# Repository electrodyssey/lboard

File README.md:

# lboard
Very basic Spartan-6 LX9 board with a plenty of GPIO
This was my very first attempt to dive into fpga world.
Board is working, however it has a few disadvantages:
Configuration is loaded via slave select-map setup which occupies a lot of fpga pins
Configuration is slow - around 3 seconds. That's an outcome of Atmega's slow gpio
There is no switched step-down psu on the board, power is regulated with a linear ldo

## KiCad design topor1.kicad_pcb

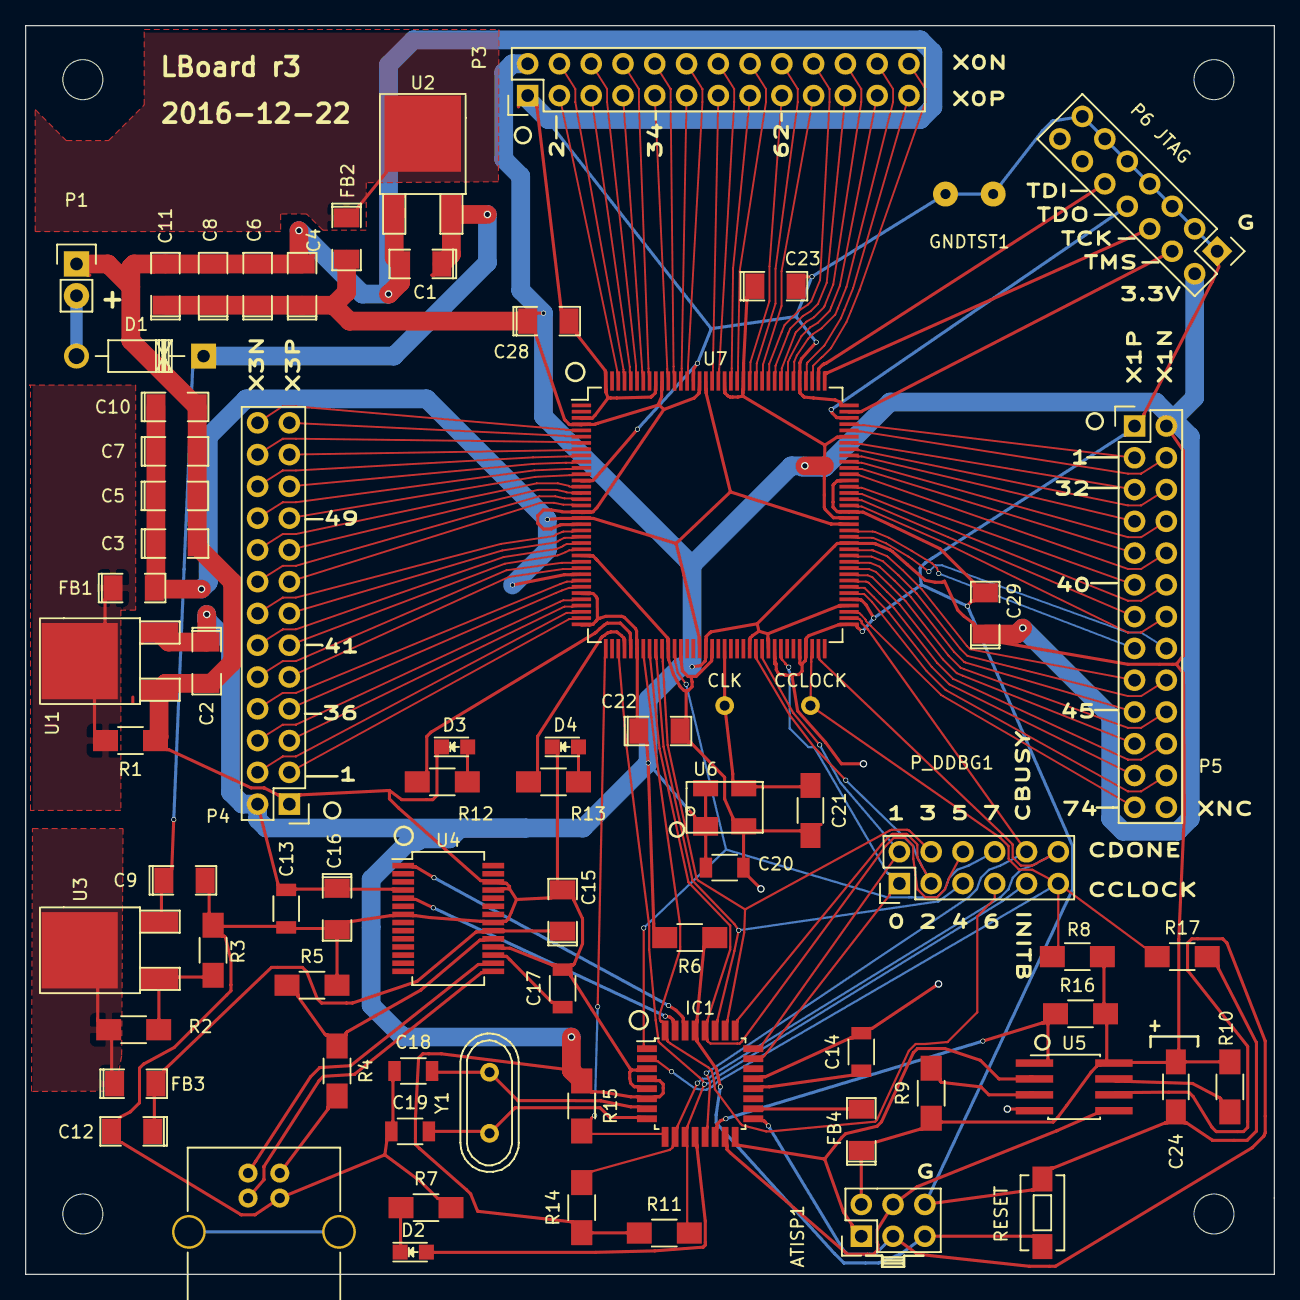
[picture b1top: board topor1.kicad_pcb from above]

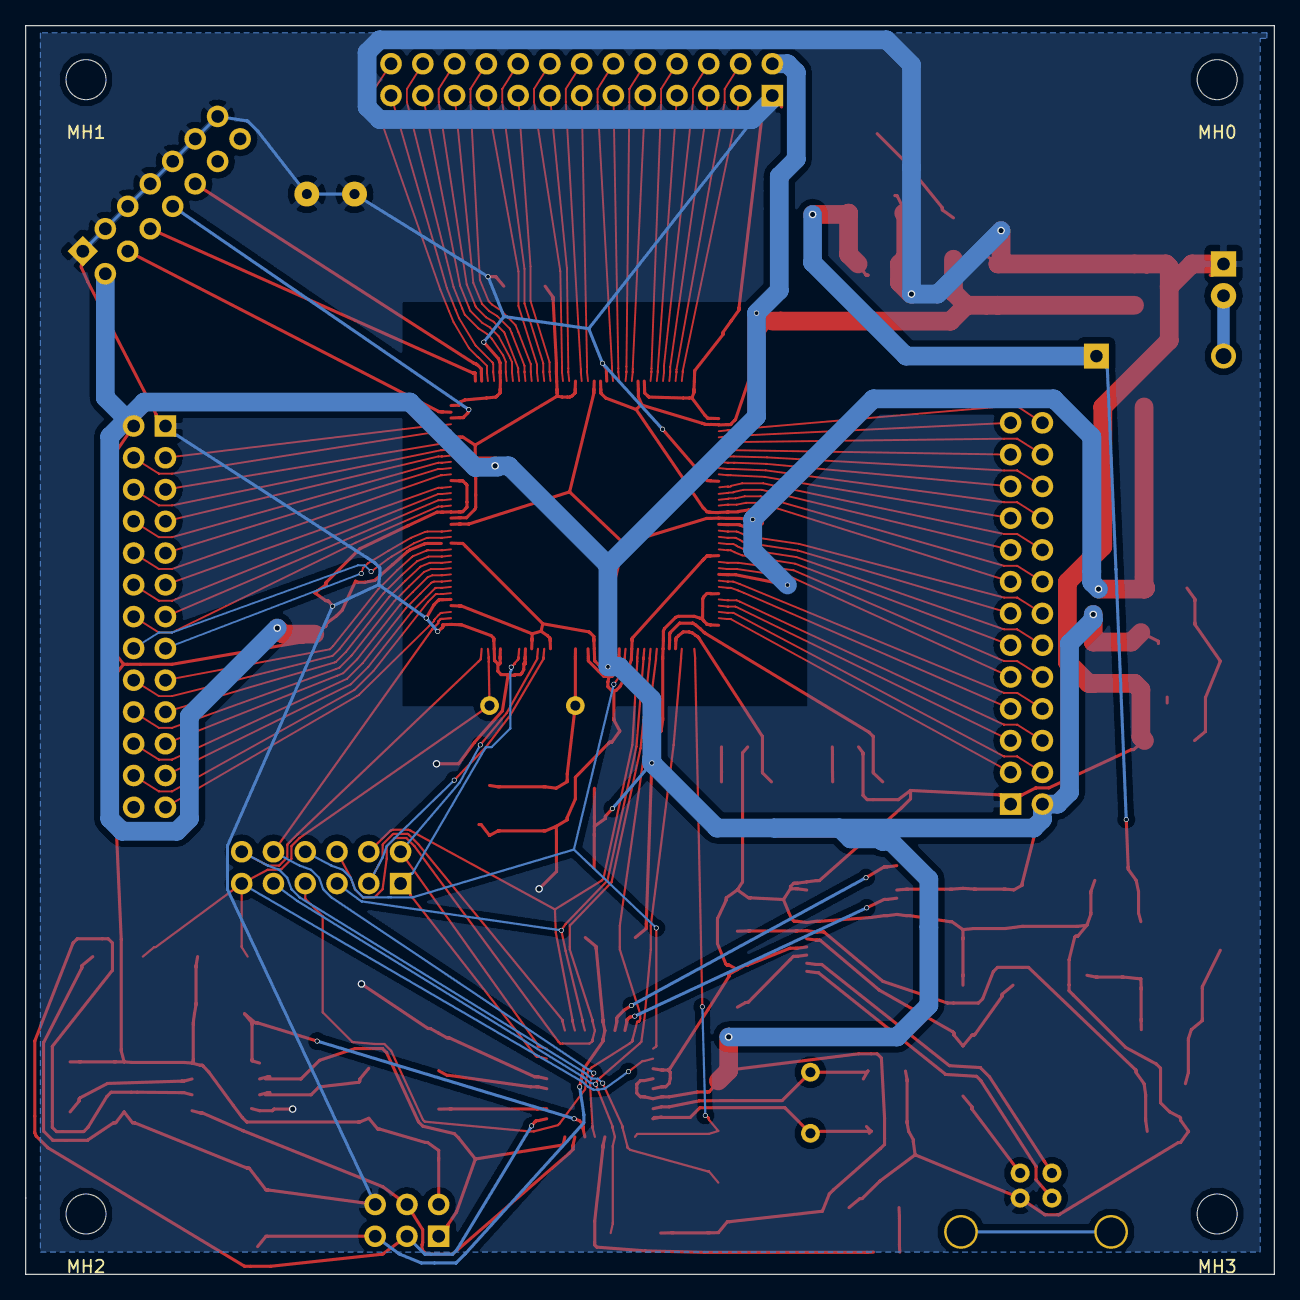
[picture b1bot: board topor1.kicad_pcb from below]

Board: 2 copper layers, 99.8 x 99.8 mm, 76 parts (4 on the bottom side), 123 nets.

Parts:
ATISP1: AVR-ISP-6; Pin_Header_Straight_2x03
C1, C2, C5, C6, C7, C8, C9, C10, C11, C22, C23, C28, C29: 10uF; SMD-1206_Pol
C3, C4, C12, C15, C16: 1uF; SMD-1206_Pol
C13, C14, C17, C20: 0.1; C_1206
C18, C19: 15pF; C_1206
C21: 15pF; C_1206_HandSoldering
C24: 1uF; C_1206_HandSoldering
CCLOCK: TEST_1P; Measurement_Point_Round-TH_Small
CLK: TEST_1P; Measurement_Point_Round-TH_Small
D1: D_Rectifier; Diode_DO-41_SOD81_Horizontal_RM10
D2: LED; LED_0805
D3, D4: Led_Small; LED_0805
FB1, FB2, FB3, FB4: FERRITE; SMD-1206_Pol
GNDTST1: TEST; SolderWirePad_2x_0-8mmDrill
IC1: ATMEGA168-A; TQFP-32_7x7mm_Pitch0.8mm
MH0, MH1, MH2, MH3: MountingHole_3.2mm_M3
P1: CONN_01X02_PWR; Pin_Header_Straight_1x02
P2: USB_B
P3: CONN_02X13_X0; Pin_Header_Straight_2x13
P4: CONN_02X13_X3; Pin_Header_Straight_2x13
P5: CONN_02X13_X1; Pin_Header_Straight_2x13
P6 JTAG: CONN_02X07_JTAG; Pin_Header_Straight_2x07
P_DDBG1: CONN_02X06; Pin_Header_Straight_2x06
R1, R2: 121; R_1206_HandSoldering
R3: 365; R_1206_HandSoldering
R4, R11, R15: 4k7; R_1206_HandSoldering
R5, R6, R8, R9, R10: 10k; R_1206_HandSoldering
R7: 220; R_1206_HandSoldering
R12, R13, R14: 330; R_1206_HandSoldering
R16, R17: 100; R_1206_HandSoldering
RESET: SW_RESET; SW_SPST_EVQPE1
U1, U3: AP1117_ADJ; TO-252-2Lead
U2: AP1117_33; TO-252-2Lead
U4: FT232RL; SSOP-28_5.3x10.2mm_Pitch0.65mm
U5: M25P16-VME; SOIC-8_5.49x5.49mm_Pitch1.27mm
U6: ECS-3963; ECS396x
U7: XC6SLX9-TQG144; LQFP-144_20x20mm_Pitch0.5mm
Y1: 11.059MHz; Crystal_HC49-U_Vertical

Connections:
+1V2: C3.1, C5.1, C7.1, C10.1, FB1.2, U7.19, U7.28, U7.52, U7.89, U7.128
+3V3: ATISP1.2, C2.1, C4.1, C6.1, C8.1, C11.1, C13.1, C16.1, C20.1, C22.1, C23.1, C24.2, C28.1, C29.1, FB2.2, FB4.1, IC1.4, IC1.6, P3.2, P4.2, P5.2, P6 JTAG.2, R6.2, R8.2, R9.1, R10.1, R11.1, R14.1, R15.1, R16.1, U1.3, U4.4, U5.8, U6.1, U6.4, U7.4, U7.18, U7.20, U7.31, U7.36, U7.42, U7.53, U7.60, U7.63, U7.76, U7.86, U7.90, U7.103, U7.122, U7.125, U7.129, U7.135
+5V: C12.1, C15.1, FB3.2, U4.20
/mcu/CBUSY: IC1.13, P_DDBG1.10, U7.74
/mcu/CCLOCK: CCLOCK.1, IC1.2, P_DDBG1.11, R16.2, R17.1, U7.70
/mcu/CD0: IC1.23, P_DDBG1.1, U7.65
/mcu/CD1: IC1.24, P_DDBG1.2, U7.62
/mcu/CD2: IC1.25, P_DDBG1.3, U7.61
/mcu/CD3: IC1.26, P_DDBG1.4, U7.46
/mcu/CD4: IC1.27, P_DDBG1.5, U7.45
/mcu/CD5: IC1.28, P_DDBG1.6, U7.44
/mcu/CD6: IC1.32, P_DDBG1.7, U7.43
/mcu/CD7: IC1.1, P_DDBG1.8, U7.48
/mcu/CDONE: IC1.10, P_DDBG1.12, R14.2, U7.71
/mcu/CINITB: IC1.11, P_DDBG1.9, R11.2, U7.39
/mcu/CPROGB: IC1.9, R15.2, U7.37
/mcu/MISO: ATISP1.1, IC1.16, U5.2
/mcu/MOSI: ATISP1.4, IC1.15, U5.5
/spartan6/CLK_XO: C21.1, CLK.1, U6.3, U7.56
/spartan6/TCK: P6 JTAG.6, U7.109
/spartan6/TDI: P6 JTAG.10, U7.110
/spartan6/TDO: P6 JTAG.8, U7.106
/spartan6/TMS: P6 JTAG.4, U7.107
/spartan6/X0_L2_N: P3.4, U7.141
/spartan6/X0_L2_P: P3.3, U7.142
/spartan6/X0_L3_N: P3.6, U7.139
/spartan6/X0_L3_P: P3.5, U7.140
/spartan6/X0_L4_N: P3.8, U7.137
/spartan6/X0_L4_P: P3.7, U7.138
/spartan6/X0_L34_N: P3.10, U7.133
/spartan6/X0_L34_P: P3.9, U7.134
/spartan6/X0_L35_N: P3.12, U7.131
/spartan6/X0_L35_P: P3.11, U7.132
/spartan6/X0_L36_N: P3.14, U7.126
/spartan6/X0_L36_P: P3.13, U7.127
/spartan6/X0_L37_N: P3.16, U7.123
/spartan6/X0_L37_P: P3.15, U7.124
/spartan6/X0_L62_N: P3.18, U7.120
/spartan6/X0_L62_P: P3.17, U7.121
/spartan6/X0_L63_N: P3.20, U7.118
/spartan6/X0_L63_P: P3.19, U7.119
/spartan6/X0_L64_N: P3.22, U7.116
/spartan6/X0_L64_P: P3.21, U7.117
/spartan6/X0_L65_N: P3.24, U7.114
/spartan6/X0_L65_P: P3.23, U7.115
/spartan6/X0_L66_N: P3.26, U7.111
/spartan6/X0_L66_P: P3.25, U7.112
/spartan6/X1_L1_N: P5.4, U7.104
/spartan6/X1_L1_P: P5.3, U7.105
/spartan6/X1_L32_N: P5.6, U7.101
/spartan6/X1_L32_P: P5.5, U7.102
/spartan6/X1_L33_N: P5.8, U7.99
/spartan6/X1_L33_P: P5.7, U7.100
/spartan6/X1_L34_N: P5.10, U7.97
/spartan6/X1_L34_P: P5.9, U7.98
/spartan6/X1_L40_N: P5.12, U7.94
/spartan6/X1_L40_P: P5.11, U7.95
/spartan6/X1_L41_N: P5.14, U7.92
/spartan6/X1_L41_P: P5.13, U7.93
/spartan6/X1_L42_N: P5.16, U7.87
/spartan6/X1_L42_P: P5.15, U7.88
/spartan6/X1_L43_N: P5.18, U7.84
/spartan6/X1_L43_P: P5.17, U7.85
/spartan6/X1_L45_N: P5.20, U7.82
/spartan6/X1_L45_P: P5.19, U7.83
/spartan6/X1_L46_N: P5.22, U7.80
/spartan6/X1_L46_P: P5.21, U7.81
/spartan6/X1_L47_N: P5.24, U7.78
/spartan6/X1_L47_P: P5.23, U7.79
/spartan6/X1_L74_P: P5.25, U7.75
/spartan6/X3_L1_N: P4.4, U7.34
/spartan6/X3_L1_P: P4.3, U7.35
/spartan6/X3_L2_N: P4.6, U7.32
/spartan6/X3_L2_P: P4.5, U7.33
/spartan6/X3_L36_N: P4.8, U7.29
/spartan6/X3_L36_P: P4.7, U7.30
/spartan6/X3_L37_N: P4.10, U7.26
/spartan6/X3_L37_P: P4.9, U7.27
/spartan6/X3_L41_N: P4.12, U7.23
/spartan6/X3_L41_P: P4.11, U7.24
/spartan6/X3_L42_N: P4.14, U7.21
/spartan6/X3_L42_P: P4.13, U7.22
/spartan6/X3_L43_N: P4.16, U7.16
/spartan6/X3_L43_P: P4.15, U7.17
/spartan6/X3_L44_N: P4.18, U7.14
/spartan6/X3_L44_P: P4.17, U7.15
/spartan6/X3_L49_N: P4.20, U7.11
/spartan6/X3_L49_P: P4.19, U7.12
/spartan6/X3_L50_N: P4.22, U7.9
/spartan6/X3_L50_P: P4.21, U7.10
/spartan6/X3_L51_N: P4.24, U7.7
/spartan6/X3_L51_P: P4.23, U7.8
/spartan6/X3_L52_N: P4.26, U7.5
/spartan6/X3_L52_P: P4.25, U7.6
GND: ATISP1.6, C1.2, C2.2, C3.2, C4.2, C5.2, C6.2, C7.2, C8.2, C9.2, C10.2, C11.2, C12.2, C13.2, C14.2, C15.2, C16.2, C17.2, C18.1, C19.1, C20.2, C21.2, C22.2, C23.2, C24.1, C28.2, C29.2, D3.1, D4.1, GNDTST1.1, IC1.3, IC1.5, IC1.21, P1.1, P2.4, P3.1, P4.1, P5.1, P6 JTAG.1, P6 JTAG.3, P6 JTAG.5, P6 JTAG.7, P6 JTAG.9, P6 JTAG.11, P6 JTAG.13, R1.1, R3.2, R5.2, R7.2, R17.2, RESET.2, U1.1, U2.1, U4.7, U4.18, U4.21, U4.25, U4.26, U5.4, U6.2, U7.3, U7.13, U7.25, U7.47, U7.49, U7.54, U7.64, U7.68, U7.69, U7.73, U7.77, U7.91, U7.96, U7.108, U7.113, U7.130, U7.136, U7.144
unnamed: ATISP1.3, IC1.17, U5.6
unnamed: ATISP1.5, IC1.29, R6.1, RESET.1
unnamed: C14.1, IC1.20
unnamed: C17.1, U4.17
unnamed: C18.2, IC1.7, Y1.2
unnamed: C19.2, IC1.8, Y1.1
unnamed: D1.2, P1.2
unnamed: D2.1, R7.1
unnamed: D2.2, IC1.12
unnamed: D3.2, R12.2
unnamed: D4.2, R13.2
unnamed: FB1.1, R1.2, U1.2
unnamed: FB2.1, U2.2
unnamed: FB3.1, R2.1, U3.2
unnamed: FB4.2, IC1.18
unnamed: IC1.14, R8.1, U5.1
unnamed: IC1.30, U4.1
unnamed: IC1.31, U4.5
unnamed: P2.1, R4.2
unnamed: P2.2, U4.16
unnamed: P2.3, U4.15
unnamed: R2.2, R3.1, U3.1
unnamed: R4.1, R5.1, U4.19
unnamed: R9.2, U5.3
unnamed: R10.2, U5.7
unnamed: R12.1, U7.41
unnamed: R13.1, U7.40
VCC: C1.1, C9.1, D1.1, U2.3, U3.3

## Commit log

2016-12-07 Initial import
2016-12-12 minor changes in silkscreen
2016-12-20 C24 was changed to an electrolytic capacitor
2016-12-20 Spartan-6 chip position was changed to avoid problems with a bent tracks. CD6 net was rerouted.
2016-12-20 bumped revision number, made some minort track layout changes
2016-12-21 footprint of oscillator Y1 changed. Some silscreen changes
2016-12-22 New footprint for SOIC-8W.
2016-12-22 ATMEGA168 description was changed to ATMEGA328P
2016-12-22 Silkscreen changes
2016-12-22 correction in silkscreen
2018-09-20 summary note
2018-09-20 summary
2018-09-20 summary message
